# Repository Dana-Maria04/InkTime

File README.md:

# InkTime

## Block Diagram

Managed by the nRF52840 SoC, the device employs an RT6160 regulator to provide a steady 3.3V supply to all peripherals. The architecture combines an e-paper display and IMU with haptic feedback and dedicated user buttons.

## Bill of Materials (BOM)
| Qty | Value             | Parts                                                                     | Device                              | Package                      | Product Link                                                                        | Datasheet Link                                                                                                                                   |
| --: | ----------------- | ------------------------------------------------------------------------- | ----------------------------------- | ---------------------------- | ----------------------------------------------------------------------------------- | ------------------------------------------------------------------------------------------------------------------------------------------------ |
|   1 | nRF52840-QIAA     | U1                                                                        | NORDIC_NRF_4_NRF52840_QF            | AQFN-73-EP(7x7)              | [JLCPCB](https://jlcpcb.com/partdetail/NordicSemicon-NRF52840_QIAAR/C190794)        | [Datasheet](https://infocenter.nordicsemi.com/pdf/nRF52840_PS_v1.9.pdf)                                                                          |
|   1 | BQ25180YBGR       | IC1                                                                       | BQ25180YBGR                         | DSBGA-8(1.1x1.6)             | [JLCPCB](https://jlcpcb.com/partdetail/TexasInstruments-BQ25180YBGR/C3682423)       | [Datasheet](https://www.ti.com/lit/ds/symlink/bq25180.pdf)                                                                                       |
|   1 | MAX17048G+T10     | U3                                                                        | ESP32_C6_LIBRARY_MAX17048G+T10      | DFN-8-EP(2x2)                | [JLCPCB](https://jlcpcb.com/partdetail/MaximIntegrated-MAX17048GT10/C2682616)       | [Datasheet](https://www.analog.com/media/en/technical-documentation/data-sheets/MAX17048-MAX17049.pdf)                                           |
|   1 | DRV2605YZFR       | IC2                                                                       | DRV2605YZFR                         | DSBGA-9                      | [JLCPCB](https://jlcpcb.com/partdetail/TexasInstruments-DRV2605YZFR/C81079)         | [Datasheet](https://www.ti.com/lit/ds/symlink/drv2605.pdf)                                                                                       |
|   1 | DMG2305UX-7       | P-channel MOSFET                                                          | DMG2305UX-7                         | SOT-23                       | [JLCPCB](https://jlcpcb.com/partdetail/HXYMOSFET-DMG2305UX7/C5261054)               | [Datasheet](https://www.diodes.com/assets/Datasheets/DMG2305UX.pdf)                                                                              |
|   1 | SI1308EDL-T1-GE3  | Q3                                                                        | ESP32_C6_LIBRARY_6_SI1308EDL-T1-GE3 | SOT-323                      | [JLCPCB](https://jlcpcb.com/partdetail/TECHPUBLIC-SI1308EDL/C7603347)               | [Datasheet](https://www.vishay.com/docs/63399/si1308edl.pdf)                                                                                     |
|   3 | MBR0530           | D2, D4, D5                                                                | MBR0530                             | SOD-123                      | [JLCPCB](https://jlcpcb.com/partdetail/4324765-MBR0530_F20000HF/C3757235)           | [Datasheet](https://wmsc.lcsc.com/wmsc/upload/file/pdf/v2/lcsc/2205311800_Yangzhou-Yangjie-Electronic-Technology-MBR0530-F2-0000HF_C3757235.pdf) |
|   1 | USBLC6-2SC6Y      | D3                                                                        | USBLC6-2SC6Y                        | SOT-23-6                     | [JLCPCB](https://jlcpcb.com/partdetail/TECHPUBLIC-USBLC62SC6Y/C5310974)             | [Datasheet](https://wmsc.lcsc.com/wmsc/upload/file/pdf/v2/lcsc/2401261525_TECH-PUBLIC-USBLC6-2SC6Y_C5310974.pdf)                                 |
|   1 | 2450AT18B100E     | ANT1                                                                      | 2450AT18B100E_2450AT18B100E         | ANTC3216X140N / 1206 class   | [JLCPCB](https://jlcpcb.com/partdetail/JohansonTechnology-2450AT18B100/C2836414)    | [Datasheet](https://www.johansontechnology.com/datasheets/antennas/2450AT18B100.pdf)                                                             |
|   1 | KH-TYPE-C-16P     | J4                                                                        | KH-TYPE-C-16P_KH-TYPE-C-16P         | SMD                          | [JLCPCB](https://jlcpcb.com/partdetail/KH-TYPE-C-16P/C709357)                       | [Datasheet](https://wmsc.lcsc.com/wmsc/upload/file/pdf/v2/lcsc/2204251630_SHENZHEN-KINGHELM-Elec-KH-TYPE-C-16P_C709357.pdf)                      |
|   3 | EVP-AKE31A        | SW_DN, SW_ENT, SW_UP                                                      | EVP-AKE31A                          | SW_EVP-AKE31A_PAN            | [JLCPCB](https://jlcpcb.com/partdetail/PANASONIC-EVPAKE31A/C569760)                 | [Datasheet](https://www.lcsc.com/datasheet/C569760.pdf)                                                                                          |
|   1 | FTC252012SR47MBCA | L7                                                                        | MLP2016SR47MT0S1_FTC252012SR47MBCA  | INDC2016X100N                | [JLCPCB](https://jlcpcb.com/partdetail/6763488-FTC252012SR47MBCA/C5832368)          | [Datasheet](https://wmsc.lcsc.com/wmsc/upload/file/pdf/v2/lcsc/2311271530_TDK-FTC252012SR47MBCA_C5832368.pdf)                                    |
|   1 | 32.768 kHz        | X2                                                                        | NORDIC_NRF_1_XTAL_32KHZ             | SMD3215-2P                   | [JLCPCB](https://jlcpcb.com/partdetail/NDK-NX3215SA_32_768K_STD_MUA9/C519280)       | [Datasheet](https://www.ndk.com/images/products/crystal/resonator/NX3215SA_e.pdf)                                                                |
|   6 | 10K               | R2_EP_DR, R5, R7, R8, R9, R_PWR_EPD                                       | RC0201FR-1310KL                     | 0201                         | [JLCPCB](https://jlcpcb.com/partdetail/YAGEO-RC0201FR1310KL/C6373588)               | [Datasheet](https://www.lcsc.com/datasheet/C6373588.pdf)                                                                                         |
|   2 | 5K1               | R1_USB, R2_USB                                                            | RC0201FR-075K1L                     | 0201                         | [JLCPCB](https://jlcpcb.com/partdetail/YAGEO-RC0201FR075K1L/C274341)                | [Datasheet](https://www.lcsc.com/datasheet/C274341.pdf)                                                                                          |
|   2 | 3K3               | R17, R18                                                                  | RNCF0201DTC3K30                     | 0201                         | [JLCPCB](https://jlcpcb.com/partdetail/SEI_Stackpole_Elec-RNCF0201DTC3K30/C2487997) | [Datasheet](https://www.lcsc.com/datasheet/C2487997.pdf)                                                                                         |
|   3 | 0R                | R2, R3, R4                                                                | 0201WMJ0000TCE                      | 0201                         | [JLCPCB](https://jlcpcb.com/partdetail/25793-0201WMJ0000TCE/C25050)                 | [Datasheet](https://www.lcsc.com/datasheet/C25050.pdf)                                                                                           |
|   1 | 2.2Î©              | R_TYPE_SEL                                                                | 0201WMF220KTCE                      | 0201                         | [JLCPCB](https://jlcpcb.com/partdetail/244650-0201WMF220KTCE/C247442)               | [Datasheet](https://www.lcsc.com/datasheet/C247442.pdf)                                                                                          |
|   9 | 100nF             | C5, C7, C8, C12, C19, C23, C27, C34, C42                                  | AC0201KRX6S6BB104                   | 0201                         | [JLCPCB](https://jlcpcb.com/partdetail/YAGEO-AC0201KRX6S6BB104/C3855913)            | [Datasheet](https://www.lcsc.com/datasheet/C3855913.pdf)                                                                                         |
|   4 | 12pF              | C1, C2, C17, C18                                                          | 0201N120J250CT                      | 0201                         | [JLCPCB](https://jlcpcb.com/partdetail/Walsin_TechCorp-0201N120J250CT/C424835)      | [Datasheet](https://www.lcsc.com/datasheet/C424835.pdf)                                                                                          |
|   2 | 1pF               | C3, C4                                                                    | GRM0335C1E1R0CA01J                  | 0201                         | [JLCPCB](https://jlcpcb.com/partdetail/2274979-GRM0335C1E1R0CA01J/C2182912)         | [Datasheet](https://www.lcsc.com/datasheet/C2182912.pdf)                                                                                         |
|   1 | 100pF             | C11                                                                       | 0201N101F160CT                      | 0201                         | [JLCPCB](https://jlcpcb.com/partdetail/Walsin_TechCorp-0201N101F160CT/C3847857)     | [Datasheet](https://www.lcsc.com/datasheet/C3847857.pdf)                                                                                         |
|   1 | 47nF              | C16                                                                       | C0201X5R473K160NTA                  | 0201                         | [JLCPCB](https://jlcpcb.com/partdetail/126083-C0201X5R473K160NTA/C124806)           | [Datasheet](https://www.lcsc.com/datasheet/C124806.pdf)                                                                                          |
|   1 | 1uF               | C15                                                                       | CL05A105KP5NNNC                     | 0402                         | [JLCPCB](https://jlcpcb.com/partdetail/C14445)                                      | [Datasheet](https://www.lcsc.com/datasheet/C14445.pdf)                                                                                           |
|   5 | 4.7uF             | C6, C14, C20, C21, C43                                                    | GRM155R61A475KEAAD                  | 0402                         | [JLCPCB](https://jlcpcb.com/partdetail/MurataElectronics-GRM155R61A475KEAAD/C77004) | [Datasheet](https://www.lcsc.com/datasheet/C77004.pdf)                                                                                           |
|   1 | 4.7uF / 25V       | C2-EP-DR                                                                  | C0402X5R475M250NT                   | 0402                         | [JLCPCB](https://jlcpcb.com/partdetail/SANYEAR-C0402X5R475M250NT/C2911388)          | [Datasheet](https://www.lcsc.com/datasheet/C2911388.pdf)                                                                                         |
|   9 | 1uF / 50V         | EPD_C1, EPD_C2, EPD_C6, EPD_C7, EPD_C8, EPD_C9, EPD_C10, EPD_C11, EPD_C12 | GRM155R61H105KE05D                  | 0402                         | [JLCPCB](https://jlcpcb.com/partdetail/1609005-GRM155R61H105KE05D/C1518208)         | [Datasheet](https://www.lcsc.com/datasheet/C1518208.pdf)                                                                                         |
|   2 | 10uF              | C24, C39                                                                  | 0402X106M100CT                      | 0402                         | [JLCPCB](https://jlcpcb.com/partdetail/Walsin_TechCorp-0402X106M100CT/C2992625)     | [Datasheet](https://www.lcsc.com/datasheet/C2992625.pdf)                                                                                         |
|   2 | 22uF              | C25, C33                                                                  | CL05A226MQ6ZUN8                     | 0402                         | [JLCPCB](https://jlcpcb.com/partdetail/2889851-CL05A226MQ6ZUN8/C2762589)            | [Datasheet](https://www.lcsc.com/datasheet/C2762589.pdf)                                                                                         |
|   1 | 820pF             | C9                                                                        | MA0201XF821K250                     | 0201                         | [JLCPCB](https://jlcpcb.com/partdetail/Meritek-MA0201XF821K250/C3842403)            | [Datasheet](https://www.lcsc.com/datasheet/C3842403.pdf)                                                                                         |
|   1 | 32MHz             | X1                                                                        | NX2016SA-32MHZ-STD-CZS-5            | SMD2016-4P                   | [JLCPCB](https://jlcpcb.com/partdetail/NDK-NX2016SA_32MHZ_STD_CZS5/C843260)         | [Datasheet](https://www.lcsc.com/datasheet/C843260.pdf)                                                                                          |
|   1 | 3.9nH             | L1                                                                        | VHF060303H3N9ST                     | 0201                         | [JLCPCB](https://jlcpcb.com/partdetail/153834-VHF060303H3N9ST/C142503)              | [Datasheet](https://www.lcsc.com/datasheet/C142503.pdf)                                                                                          |
|   1 | 15nH              | L3                                                                        | MLK0603L15NJT000                    | 0201                         | [JLCPCB](https://jlcpcb.com/partdetail/TDK-MLK0603L15NJT000/C6990407)               | [Datasheet](https://www.lcsc.com/datasheet/C6990407.pdf)                                                                                         |
|   1 | BMA421            | IC3                                                                       | BMA421                              | LGA-12(2x2)                  | [JLCPCB](https://jlcpcb.com/partdetail/BoschSensortec-BMA421/C5242966)              | [Datasheet](https://files.pine64.org/doc/datasheet/pinetime/BST-BMA421-FL000.pdf)                                                                |
|   1 | RT6160AWSC        | IC9                                                                       | RT6160AWSC                          | WLCSP-15B(2.3x1.4)           | [JLCPCB](https://jlcpcb.com/partdetail/RichtekTech-RT6160AWSC/C7065276)             | [Datasheet](https://www.mouser.com/datasheet/2/1458/DS6160A_03-3104604.pdf)                                                                      |
|   1 | 503480-2400       | J1                                                                        | 5034802400                          | 24-pin 0.5mm right-angle FPC | [JLCPCB](https://jlcpcb.com/partdetail/MOLEX-5034802400/C122434)                    | [Datasheet](https://www.mouser.com/datasheet/2/276/2/5034802400_FFC_FPC_CONNECTORS-1112921.pdf)                                                  |

## System Design and Hardware Implementation

The hardware architecture of the **InkTime Smartwatch** centers on the **nRF52840 microcontroller**, integrating five specialized sub-systems to create a high-efficiency wearable device.

### 1. Central SoC & Communication
The **nRF52840** handles all high-level logic, from sensor fusion to Bluetooth LE communication. It utilizes a **32 MHz crystal** for active processing and a **32.768 kHz crystal** for low-power timekeeping. For debugging and firmware updates, a **TC2030 SWD header** is included, exposing the `SWDIO` and `SWDCLK` lines.

### 2. Power Subsystem & Efficiency
Energy is managed through a multi-stage architecture:
* **USB-C Input:** Protected by **USBLC6-2SC6Y** ESD diodes to ensure safety during charging.
* **Management:** The **BQ25180 charger** regulates power flow between the USB source and the **Li-Po battery**.
* **Efficiency:** An **RT6160 Buck-Boost converter** ensures all peripherals receive exactly **3.3V**, regardless of battery discharge levels.
* **Monitoring:** The **MAX17048 fuel gauge** uses I2C to alert the MCU of low-battery conditions in real-time.

### 3. Specialized Sub-systems
* **Display:** The **1.54-inch E-Ink panel** uses an SPI interface. Its bi-stable nature allows it to hold an image without consuming power, drastically reducing the overall energy profile.
* **Motion & Interaction:** An **IMU (BMA421/423)** monitors activity, while three GPIO-mapped buttons manage user navigation and input.
* **Haptics:** Physical feedback for notifications is provided by a vibration motor controlled by the **DRV2605 driver**, which supports pre-programmed haptic patterns over I2C.

### 4. Energy Estimation
The system is optimized for an extremely low duty cycle:
* **Deep Sleep:** $< 10\text{µ}$.
* **Active Refresh:** $8\text{-}10\text{ mA}$ for approximately $1\text{-}2$ seconds per minute.

Based on the **250 mAh** battery capacity, the smartwatch achieves an autonomy of **over 9 days**, even with active sensor monitoring and daily haptic notifications. This performance highlights the synergy between the E-Ink technology and the nRF52's advanced power-saving features.

### Detailed Pinnout Map of nRF52840

| nRF52840 Pin | Connected Block | Signal Name | Purpose / Function |
| :--- | :--- | :--- | :--- |
| **P1.13** | E-paper Display | `MOSI` | SPI data output to display |
| **P1.15** | E-paper Display | `SCK` | SPI serial clock line |
| **P0.05** | E-paper Display | `EPD_CS` | SPI chip select (active low) |
| **P0.16** | E-paper Display | `EPD_DC` | Data/Command selection toggle |
| **P0.17** | E-paper Display | `EPD_RST` | Hardware reset for display |
| **P0.15** | E-paper Display | `EPD_BUSY` | Status feedback (busy/ready) |
| **P0.06** | I2C Bus (Shared) | `SDA` | Data line for IMU, Fuel Gauge, and Haptic |
| **P0.07** | I2C Bus (Shared) | `SCL` | Clock line for IMU, Fuel Gauge, and Haptic |
| **P0.08** | IMU (BMA42x) | `IMU_INT1` | Primary motion interrupt |
| **P1.08** | IMU (BMA42x) | `IMU_INT2` | Secondary motion interrupt |
| **P0.11** | PMIC (BQ25180) | `PMIC_INT` | Power-management status interrupt |
| **P0.24** | Fuel Gauge | `ALERT` | Battery fuel gauge status alert |
| **P0.12** | Haptic Driver | `HAPTIC_EN` | Enable and control for DRV2605 |
| **P0.13** | USB-C Interface | `D+` | USB differential data positive |
| **P0.14** | USB-C Interface | `D-` | USB differential data negative |
| **VBUS pin** | Charger / USB-C | `VBUS` | USB voltage presence detection |
| **SWDIO** | SWD Header | `SWDIO` | Bidirectional debug/programming data |
| **SWDCLK** | SWD Header | `SWDCLK` | Debug/programming clock reference |
| **P1.09** | SWD Header | `SWO` | Single Wire Output (trace debug) |
| **P0.18 / RESET** | SWD Header | `RESET` | Global hardware reset line |
| **ANT pin** | RF Network | `RF` | 2.4 GHz connection to chip antenna |

## Design Decisions & DRC/ERC Notes

### 1. Hardware Design Log
* **Space Optimization:** To fit the enclosure, a **1.0 mm PCB** was used with all components mounted on the **TOP layer**. The use of **0201 footprints** was critical for the high-density layout.
* **Signal Integrity:** **100 nF decoupling capacitors** are placed as close as possible ($< 0.5$ mm) to power pins. Power traces are widened to **0.3 mm** to ensure stable voltage delivery.
* **RF Layout:** The antenna is positioned on the board edge with a clear **Keep-out zone** (no copper on any layer) to maximize Bluetooth connectivity.

### 2. Validation & Manual Approvals
The following CAD warnings were reviewed and approved based on project constraints:

* **Mechanical Alignment (DRC):** Dimension errors for the **USB-C connector and tactile buttons** were ignored because their placement must match the pre-defined enclosure openings.
* **High-Density Routing (DRC):** Overlaps caused by **via-in-pad** and escape routing for the nRF52840 were accepted. This was the only way to route the MCU pins in the available space.
* **Net Connectivity (ERC):** "Only INPUT pins" warnings were verified; the schematic is functionally complete, and these are typical false positives in this project context.
* **Power Pins (ERC):** Power rail warnings were manually checked to ensure that the **RT6160** and **BQ25180** correctly supply the 3.3V and VBAT nets.

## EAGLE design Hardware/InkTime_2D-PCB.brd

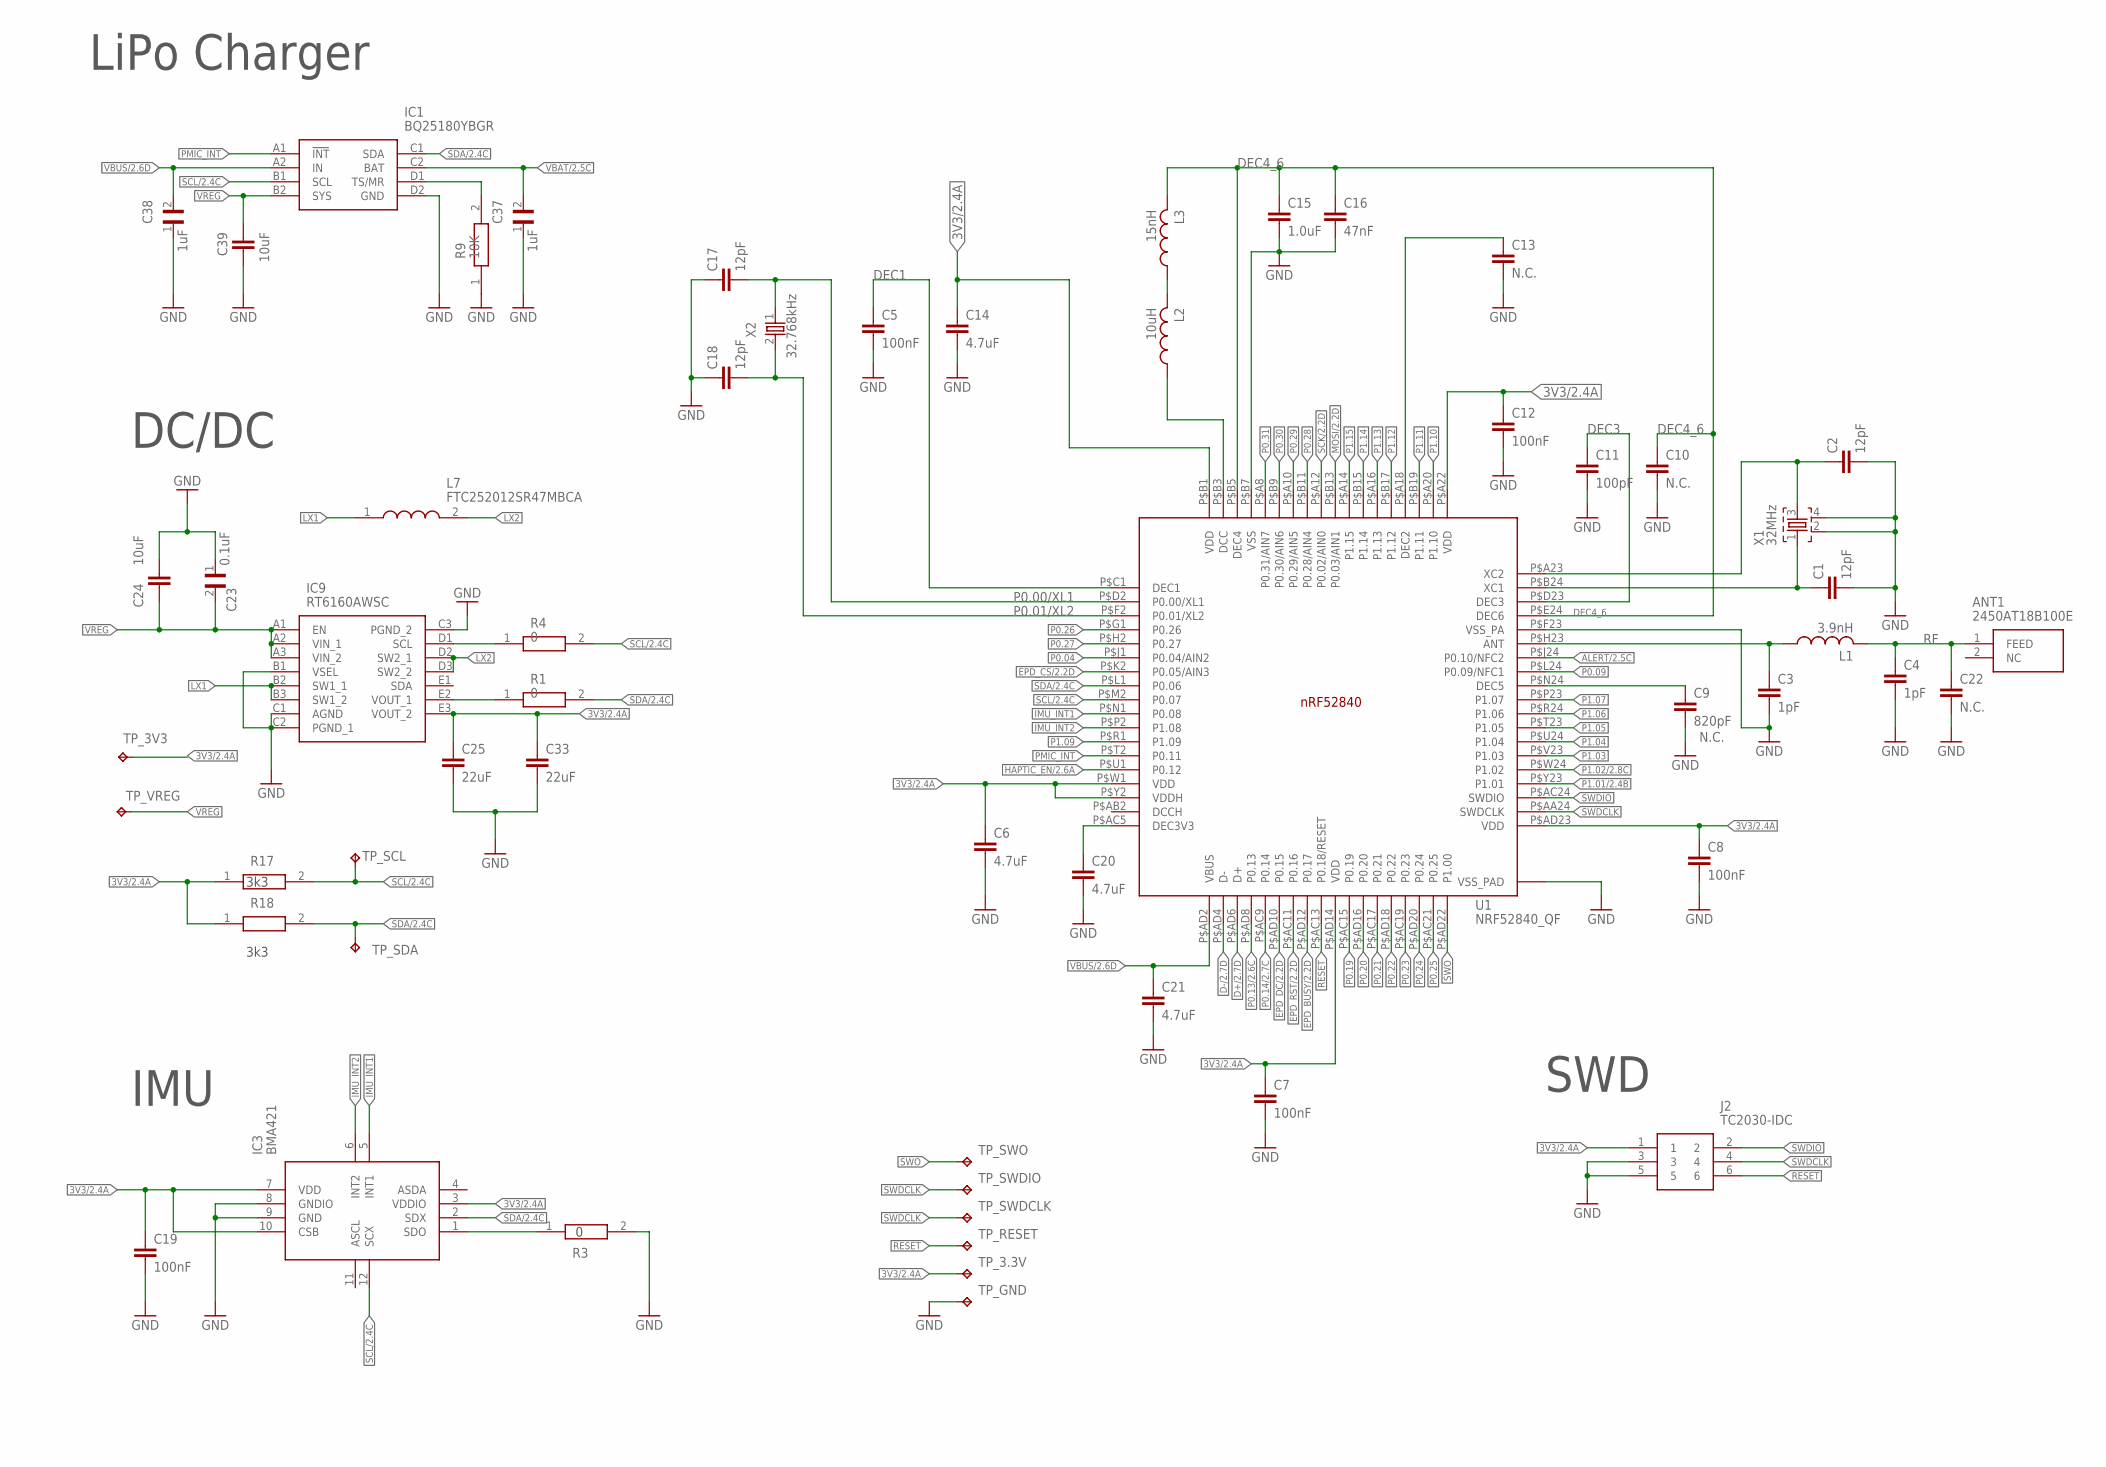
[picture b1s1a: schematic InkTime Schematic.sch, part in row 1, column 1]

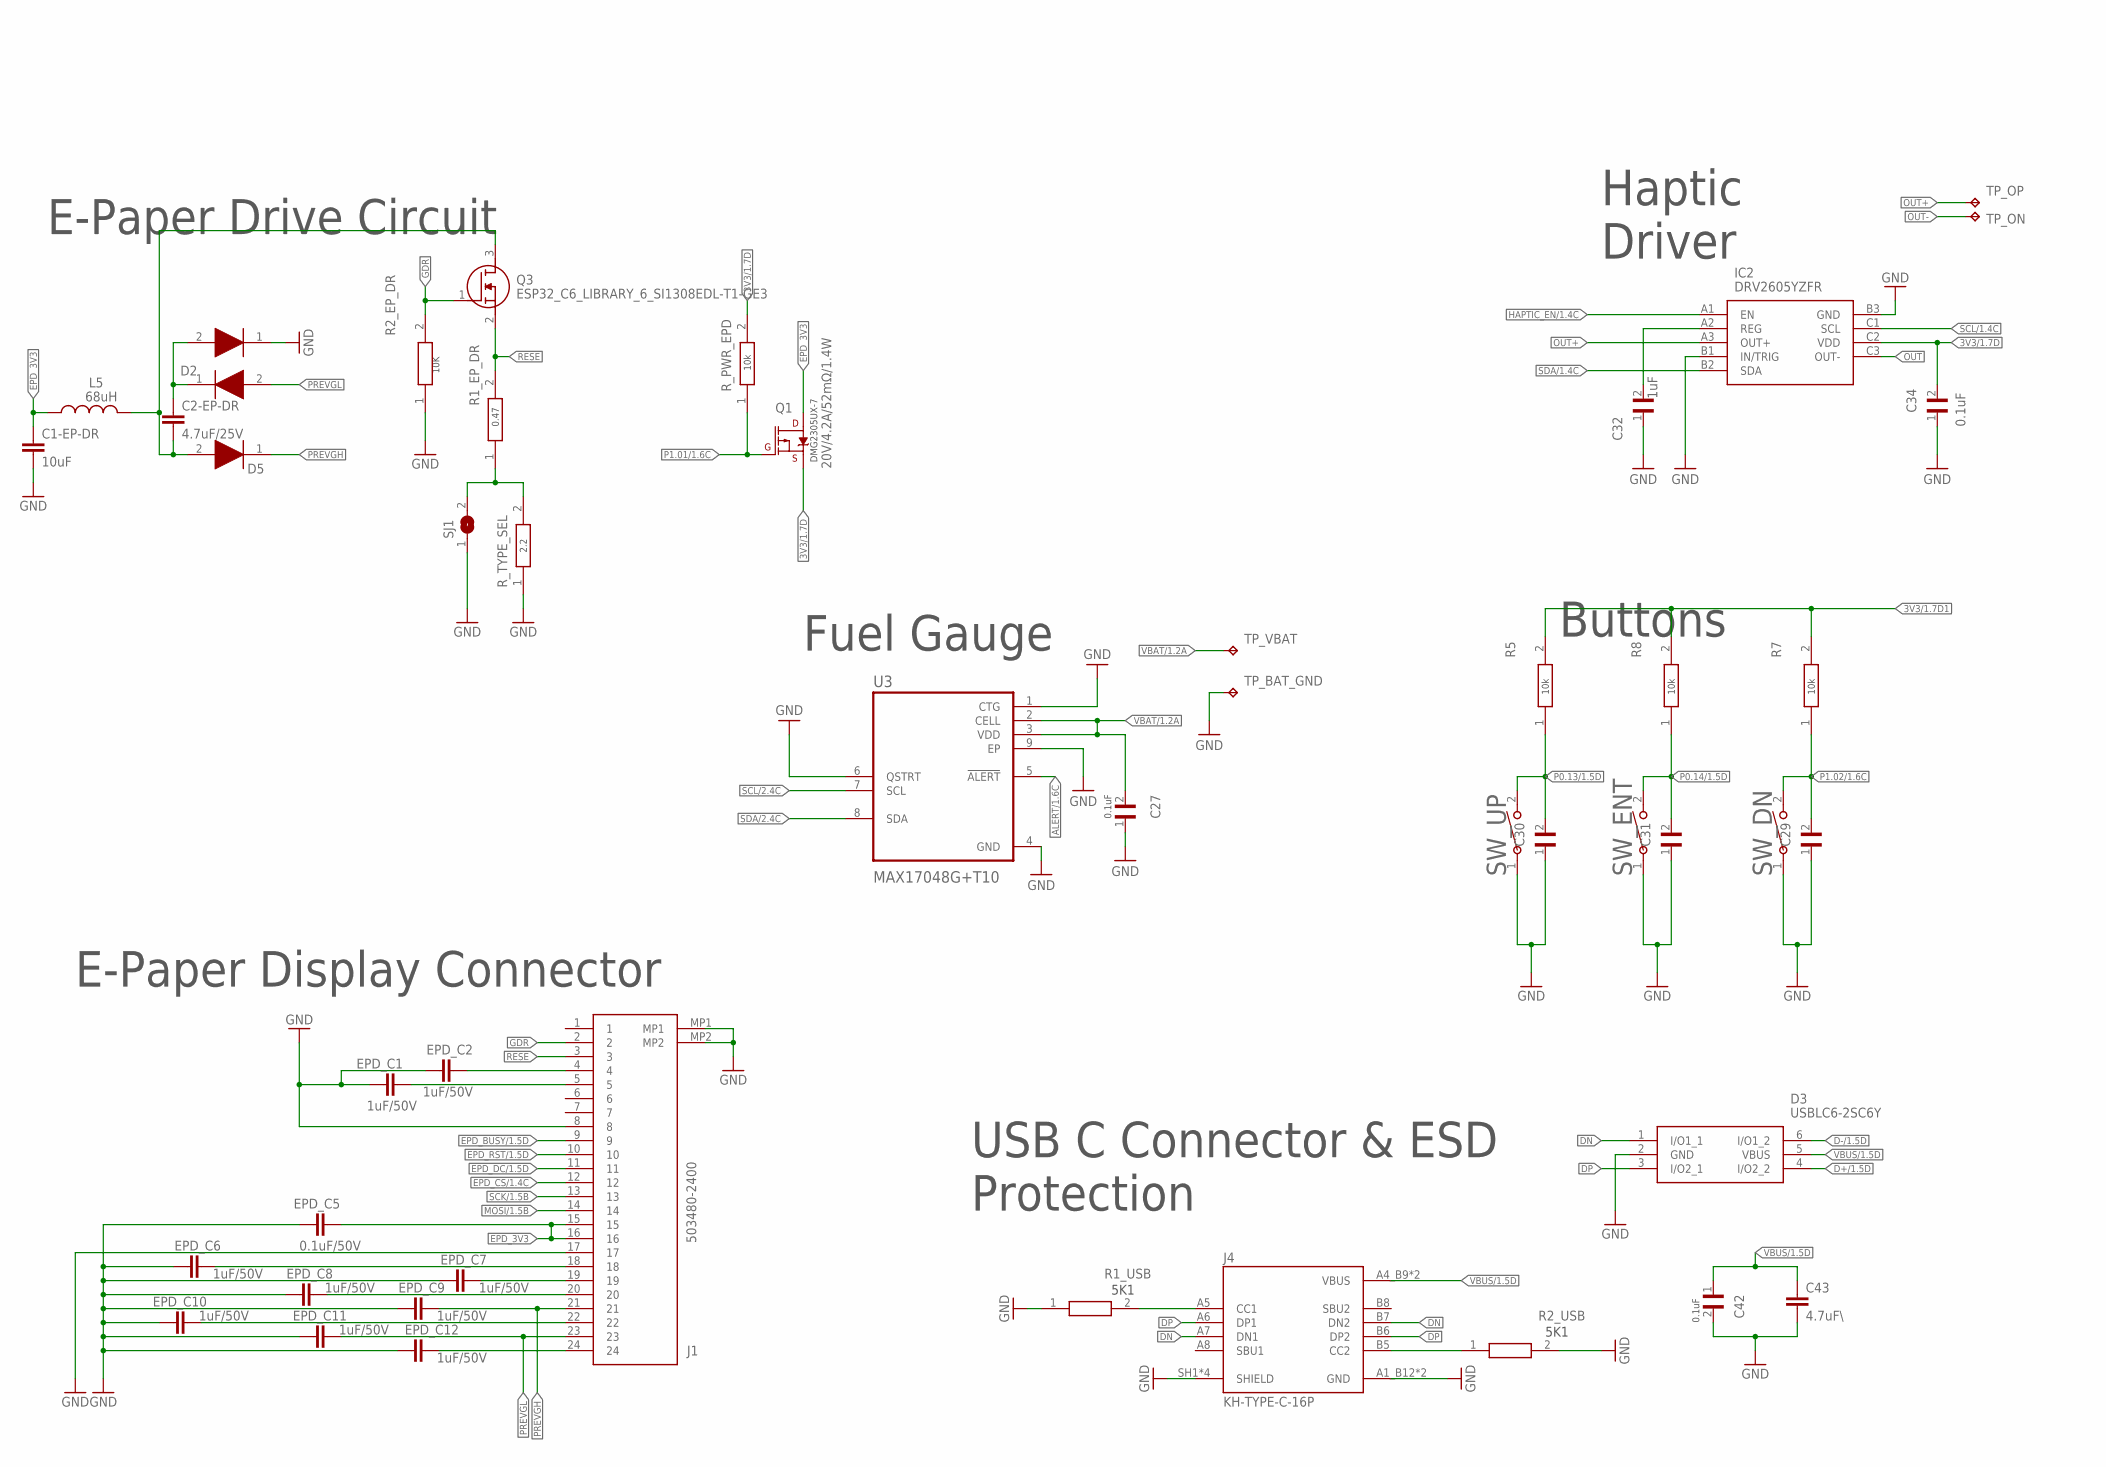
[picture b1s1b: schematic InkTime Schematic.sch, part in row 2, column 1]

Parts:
ANT1: 2450AT18B100E; 2450AT18B100E_ANTC3216X140N
C1, C2, C17, C18: 12pF; NORDIC_NRF_3_RESC0201_L
C1-EP-DR, C24, C39: 10uF; NORDIC_NRF_3_RESC0402_L
C2-EP-DR: 4.7uF/25V; NORDIC_NRF_3_RESC0402_L
C3, C4: 1pF; NORDIC_NRF_3_RESC0201_L
C5, C7, C8, C12, C19: 100nF; NORDIC_NRF_3_RESC0201_L
C6, C14: 4.7uF; NORDIC_NRF_3_RESC0402_L
C9: 820pF; NORDIC_NRF_3_RESC0201_L
C10, C13, C22: N.C.; NORDIC_NRF_3_RESC0201_L
C11: 100pF; NORDIC_NRF_3_RESC0201_L
C15: 1.0uF; NORDIC_NRF_3_RESC0402_L
C16: 47nF; NORDIC_NRF_3_RESC0201_L
C20, C21: 4.7uF; PERFECT_0402_0402
C23, C27, C34: 0.1uF; GRM011R60J152KE01L_1_0201
C25, C33: 22uF; NORDIC_NRF_3_RESC0402_L
C29, C30, C31: 1uF; GRM011R60J152KE01L_2_CAPC0201X13N
C32, C37, C38: 1uF; GRM011R60J152KE01L_1_0201
C42: 0.1uF; GRM011R60J152KE01L_2_CAPC0201X13N
C43: 4.7uF\; NORDIC_NRF_3_RESC0402_L
D1: MBR0530; ESP32_C6_LIBRARY_5_SOD3716X135N
D2, D5: ESP32_C6_LIBRARY_5_MBR0530; ESP32_C6_LIBRARY_5_SOD3716X135N
D3: USBLC6-2SC6Y; ESP32_C6_LIBRARY_3_SOT95P280X145-6N
EPD_C1, EPD_C2, EPD_C6, EPD_C7, EPD_C8, EPD_C9, EPD_C10, EPD_C11, EPD_C12: 1uF/50V; NORDIC_NRF_3_RESC0402_L
EPD_C5: 0.1uF/50V; NORDIC_NRF_3_RESC0201_L
IC1: BQ25180YBGR; BQ25180YBGR_BGA8C40P2X4_100X155X50
IC2: DRV2605YZFR; DRV2605YZFR_BGA9C50P3X3_144X144X62
IC3: BMA421; BMA423_BMA423
IC9: RT6160AWSC; RT6160AWSC_BGA15C40P3X5_140X230X60
J1: 503480-2400; 503480-2400_5034802400
J2: TC2030-IDC; TC2030-IDC_TC2030IDC
J4: KH-TYPE-C-16P; KH-TYPE-C-16P_KINGHELM_KH-TYPE-C-16P
L1: 3.9nH; NORDIC_NRF_2_RESC0201_L
L2: 10uH; NORDIC_NRF_2_RESC0201_L
L3: 15nH; NORDIC_NRF_2_RESC0201_L
L5: 68uH; NORDIC_NRF_2_RESC0402_L
L7: FTC252012SR47MBCA; MLP2016SR47MT0S1_INDC2016X100N
Q1: 20V/4.2A/52mΩ/1.4W; ESP32_C6_LIBRARY_4_ESP32_C6_LIBRARY_4_ESP32_C6_LIBRARY_4_ES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
Q3: ESP32_C6_LIBRARY_6_SI1308EDL-T1-GE3; ESP32_C6_LIBRARY_6_SOT65P210X110-3N
R1, R3, R4: 0; ERA-1AEB3401C_0201
R1_EP_DR: 0.47; CPF0201D7K68C1_0201
R1_USB, R2_USB: 5K1; CPF0201D7K68C1_0201
R2_EP_DR, R5, R7, R8: 10k; CPF0201D7K68C1_0201
R9: 10K; ERA-1AEB3401C_0201
R17: 3k3; ERA-1AEB3401C_0201
R18: 3K3; ERA-1AEB3401C_0201
R_PWR_EPD: 10K; CPF0201D7K68C1_0201
R_TYPE_SEL: 2.2; CPF0201D7K68C1_0201
SJ1: ESP32_C6_LIBRARY_7_JUMPER_SJ
SW_DN: 2025-10-22_07-23-44_LIBRARY_EVP-AKE31ASW_EVP-AKE3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; 2025-10-22_07-23-44_LIBRARY_SW_EVP-AKE31A_PAN
SW_ENT: 2025-10-22_07-23-44_LIBRARY_EVP-AKE31ASW_EVP-AKE3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; 2025-10-22_07-23-44_LIBRARY_SW_EVP-AKE31A_PAN
SW_UP: 2025-10-22_07-23-44_LIBRARY_EVP-AKE31ASW_EVP-AKE3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; 2025-10-22_07-23-44_LIBRARY_SW_EVP-AKE31A_PAN
TP_3.3V, TP_3V3: HECTOR_WATCH_1_TPTP20R; HECTOR_WATCH_1_TP20R
TP_BAT_GND: HECTOR_WATCH_1_TPTP20R; HECTOR_WATCH_1_TP20R
TP_GND: HECTOR_WATCH_1_TPTP20R; HECTOR_WATCH_1_TP20R
TP_ON: HECTOR_WATCH_1_TPTP20R; HECTOR_WATCH_1_TP20R
TP_OP: HECTOR_WATCH_1_TPTP20R; HECTOR_WATCH_1_TP20R
TP_RESET: HECTOR_WATCH_1_TPTP20R; HECTOR_WATCH_1_TP20R
TP_SCL: HECTOR_WATCH_1_TPTP20R; HECTOR_WATCH_1_TP20R
TP_SDA: HECTOR_WATCH_1_TPTP20R; HECTOR_WATCH_1_TP20R
TP_SWDCLK: HECTOR_WATCH_1_TPTP20R; HECTOR_WATCH_1_TP20R
TP_SWDIO: HECTOR_WATCH_1_TPTP20R; HECTOR_WATCH_1_TP20R
TP_SWO: HECTOR_WATCH_1_TPTP20R; HECTOR_WATCH_1_TP20R
TP_VBAT: HECTOR_WATCH_1_TPTP20R; HECTOR_WATCH_1_TP20R
TP_VREG: HECTOR_WATCH_1_TPTP20R; HECTOR_WATCH_1_TP20R
U1: NRF52840_QF; NORDIC_NRF_4_AQFN50P700X700X85_HS-74N
U3: MAX17048G+T10; ESP32_C6_LIBRARY_SON50P200X200X80-9N
X1: 32MHz; NORDIC_NRF_BT-XTAL_2016_N
X2: 32.768kHz; NORDIC_NRF_1_XTAL_3215_N

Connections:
3V3/1.7D: C34.2, IC2.C2 (VDD), Q1.2 (S), R_PWR_EPD.2
3V3/1.7D1: R5.2, R7.2, R8.2
3V3/2.4A: C6.1, C7.1, C8.1, C12.1, C14.1, C19.1, C25.1, C33.1, IC3.3 (VDDIO), IC3.7 (VDD), IC3.10 (CSB), IC9.E3 (VOUT_2), J2.1, R17.1, R18.1, TP_3.3V.TP, TP_3V3.TP, U1.P$A22 (VDD), U1.P$AD14 (VDD), U1.P$AD23 (VDD), U1.P$B1 (VDD), U1.P$W1 (VDD), U1.P$Y2 (VDDH)
ALERT/1.6C: U3.5 (!ALERT)
ALERT/2.5C: U1.P$J24 (P0.10/NFC2)
D+/1.5D: D3.4 (I/O2_2)
D+/2.7D: U1.P$AD6 (D+)
D-/1.5D: D3.6 (I/O1_2)
D-/2.7D: U1.P$AD4 (D-)
DEC1: C5.1, U1.P$C1 (DEC1)
DEC3: C11.1, U1.P$D23 (DEC3)
DEC4_6: C10.1, C15.1, C16.1, L3.2, U1.P$B5 (DEC4), U1.P$E24 (DEC6)
DN: D3.1 (I/O1_1), J4.A7 (DN1), J4.B7 (DN2)
DP: D3.3 (I/O2_1), J4.A6 (DP1), J4.B6 (DP2)
EPD_3V3: C1-EP-DR.1, EPD_C5.2, J1.15, J1.16, L5.1, Q1.3 (D)
EPD_BUSY/1.5D: J1.9
EPD_BUSY/2.2D: U1.P$AD12 (P0.17)
EPD_CS/1.4C: J1.12
EPD_CS/2.2D: U1.P$K2 (P0.05/AIN3)
EPD_DC/1.5D: J1.11
EPD_DC/2.2D: U1.P$AD10 (P0.15)
EPD_RST/1.5D: J1.10
EPD_RST/2.2D: U1.P$AC11 (P0.16)
GDR: J1.2, Q3.1 (G), R2_EP_DR.2
GND: C1.2, C1-EP-DR.2, C2.2, C3.2, C4.2, C5.2, C6.2, C7.2, C8.2, C11.2, C12.2, C13.2, C14.2, C17.1, C18.1, C19.2, C20.2, C21.2, C22.2, C23.1, C24.1, C25.2, C27.1, C29.1, C30.1, C31.1, C32.1, C33.2, C34.1, C37.1, C38.1, C39.1, C42.2, C43.2, D1.1 (K), D3.2 (GND), EPD_C1.1, EPD_C2.1, EPD_C5.1, EPD_C6.1, EPD_C7.1, EPD_C8.1, EPD_C9.1, EPD_C10.1, EPD_C11.1, EPD_C12.1, IC1.D2 (GND), IC2.B1 (IN/TRIG), IC2.B3 (GND), IC3.8 (GNDIO), IC3.9 (GND), IC9.B1 (VSEL), IC9.C1 (AGND), IC9.C2 (PGND_1), IC9.C3 (PGND_2), J1.8, J1.17, J1.MP1, J1.MP2, J2.3, J2.5, J4.A1_B12 (GND), J4.A12_B1 (GND), J4.SH1 (SHIELD), J4.SH2 (SHIELD), J4.SH3 (SHIELD), J4.SH4 (SHIELD), R1_USB.1, R2_EP_DR.1, R2_USB.2, R3.2, R9.1, R_TYPE_SEL.1, SJ1.1, SW_DN.1, SW_ENT.1, SW_UP.1, TP_BAT_GND.TP, TP_GND.TP, U1.P$74 (VSS_PAD), U1.P$75 (VSS_PAD), U1.P$76 (VSS_PAD), U1.P$77 (VSS_PAD), U1.P$78 (VSS_PAD), U1.P$79 (VSS_PAD), U1.P$80 (VSS_PAD), U1.P$81 (VSS_PAD), U1.P$82 (VSS_PAD), U1.P$83 (VSS_PAD), U1.P$84 (VSS_PAD), U1.P$85 (VSS_PAD), U1.P$86 (VSS_PAD), U1.P$87 (VSS_PAD), U1.P$88 (VSS_PAD), U1.P$89 (VSS_PAD), U1.P$90 (VSS_PAD), U1.P$F23 (VSS_PA), U3.1 (CTG), U3.4 (GND), U3.6 (QSTRT), U3.9 (EP), X1.2, X1.4
HAPTIC_EN/1.4C: IC2.A1 (EN)
HAPTIC_EN/2.6A: U1.P$U1 (P0.12)
IMU_INT1: IC3.5 (INT1), U1.P$N1 (P0.08)
IMU_INT2: IC3.6 (INT2), U1.P$P2 (P1.08)
LX1: IC9.B2 (SW1_1), IC9.B3 (SW1_2), L7.1
LX2: IC9.D2 (SW2_1), IC9.D3 (SW2_2), L7.2
MOSI/1.5B: J1.14
MOSI/2.2D: U1.P$B13 (P0.03/AIN1)
unnamed: C20.1, U1.P$AC5 (DEC3V3)
unnamed: C9.1, U1.P$N24 (DEC5)
unnamed: C13.1, U1.P$A18 (DEC2)
unnamed: L2.2, L3.1
unnamed: C15.2, C16.2, U1.P$B7 (VSS)
unnamed: L2.1, U1.P$B3 (DCC)
unnamed: C3.1, L1.1, U1.P$H23 (ANT)
unnamed: C2.1, U1.P$A23 (XC2), X1.3
unnamed: C1.1, U1.P$B24 (XC1), X1.1
unnamed: EPD_C2.2, J1.4
unnamed: IC9.D1 (SCL), R4.1
unnamed: EPD_C10.2, J1.22
unnamed: IC9.E2 (VOUT_1), R1.1
unnamed: EPD_C1.2, J1.5
unnamed: IC1.D1 (TS/MR), R9.2
unnamed: IC3.1 (SDO), R3.1
unnamed: EPD_C6.2, J1.18
unnamed: EPD_C7.2, J1.19
unnamed: EPD_C12.2, J1.24
unnamed: EPD_C8.2, J1.20
unnamed: C32.2, IC2.A2 (REG)
unnamed: C2-EP-DR.2, D5.2 (A), L5.2, Q3.3 (D)
unnamed: C2-EP-DR.1, D1.2 (A), D2.1 (K)
unnamed: R1_EP_DR.1, R_TYPE_SEL.2, SJ1.2
unnamed: J4.A5 (CC1), R1_USB.2
unnamed: J4.B5 (CC2), R2_USB.1
N.C.: C9.2, C10.2
OUT: IC2.C3 (OUT-)
OUT+: IC2.A3 (OUT+), TP_OP.TP
OUT-: TP_ON.TP
P0.00/XL1: C17.2, U1.P$D2 (P0.00/XL1), X2.1
P0.01/XL2: C18.2, U1.P$F2 (P0.01/XL2), X2.2
P0.04: U1.P$J1 (P0.04/AIN2)
P0.09: U1.P$L24 (P0.09/NFC1)
P0.13/1.5D: C30.2, R5.1, SW_UP.2
P0.13/2.6C: U1.P$AD8 (P0.13)
P0.14/1.5D: C31.2, R8.1, SW_ENT.2
P0.14/2.7C: U1.P$AC9 (P0.14)
P0.19: U1.P$AC15 (P0.19)
P0.20: U1.P$AD16 (P0.20)
P0.21: U1.P$AC17 (P0.21)
P0.22: U1.P$AD18 (P0.22)
P0.23: U1.P$AC19 (P0.23)
P0.24: U1.P$AD20 (P0.24)
P0.25: U1.P$AC21 (P0.25)
P0.26: U1.P$G1 (P0.26)
P0.27: U1.P$H2 (P0.27)
P0.28: U1.P$B11 (P0.28/AIN4)
P0.29: U1.P$A10 (P0.29/AIN5)
P0.30: U1.P$B9 (P0.30/AIN6)
P0.31: U1.P$A8 (P0.31/AIN7)
P1.01/1.6C: Q1.1 (G), R_PWR_EPD.1
P1.01/2.4B: U1.P$Y23 (P1.01)
P1.02/1.6C: C29.2, R7.1, SW_DN.2
P1.02/2.8C: U1.P$W24 (P1.02)
P1.03: U1.P$V23 (P1.03)
P1.04: U1.P$U24 (P1.04)
P1.05: U1.P$T23 (P1.05)
P1.06: U1.P$R24 (P1.06)
P1.07: U1.P$P23 (P1.07)
P1.09: U1.P$R1 (P1.09)
P1.10: U1.P$A20 (P1.10)
P1.11: U1.P$B19 (P1.11)
P1.12: U1.P$B17 (P1.12)
P1.13: U1.P$A16 (P1.13)
P1.14: U1.P$B15 (P1.14)
P1.15: U1.P$A14 (P1.15)
PMIC_INT: IC1.A1 (!INT), U1.P$T2 (P0.11)
PREVGH: D5.1 (K), EPD_C9.2, J1.21
PREVGL: D2.2 (A), EPD_C11.2, J1.23
RESE: J1.3, Q3.2 (S), R1_EP_DR.2
RESET: J2.6, TP_RESET.TP, U1.P$AC13 (P0.18/RESET)
RF: ANT1.1 (FEED), C4.1, C22.1, L1.2
SCK/1.5B: J1.13
SCK/2.2D: U1.P$A12 (P0.02/AIN0)
SCL/1.4C: IC2.C1 (SCL)
SCL/2.4C: IC1.B1 (SCL), IC3.12 (SCX), R4.2, R17.2, TP_SCL.TP, U1.P$M2 (P0.07), U3.7 (SCL)
SDA/1.4C: IC2.B2 (SDA)
SDA/2.4C: IC1.C1 (SDA), IC3.2 (SDX), R1.2, R18.2, TP_SDA.TP, U1.P$L1 (P0.06), U3.8 (SDA)
SWDCLK: J2.4, TP_SWDCLK.TP, TP_SWDIO.TP, U1.P$AA24 (SWDCLK)
SWDIO: J2.2, U1.P$AC24 (SWDIO)
SWO: TP_SWO.TP, U1.P$AD22 (P1.00)
VBAT/1.2A: C27.2, TP_VBAT.TP, U3.2 (CELL), U3.3 (VDD)
VBAT/2.5C: C37.2, IC1.C2 (BAT)
VBUS/1.5D: C42.1, C43.1, D3.5 (VBUS), J4.A4_B9 (VBUS), J4.A9_B4 (VBUS)
VBUS/2.6D: C21.1, C38.2, IC1.A2 (IN), U1.P$AD2 (VBUS)
VREG: C23.2, C24.2, C39.2, IC1.B2 (SYS), IC9.A1 (EN), IC9.A2 (VIN_1), IC9.A3 (VIN_2), TP_VREG.TP

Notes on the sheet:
SWD
LiPo Charger
IMU
DC/DC
E-Paper Display Connector
3k3
Fuel Gauge
0.1uF
E-Paper Drive Circuit
0.47
2.2
10K
DMG2305UX-7
10k
Haptic Driver
5K1
USB C Connector & ESD Protection
Buttons

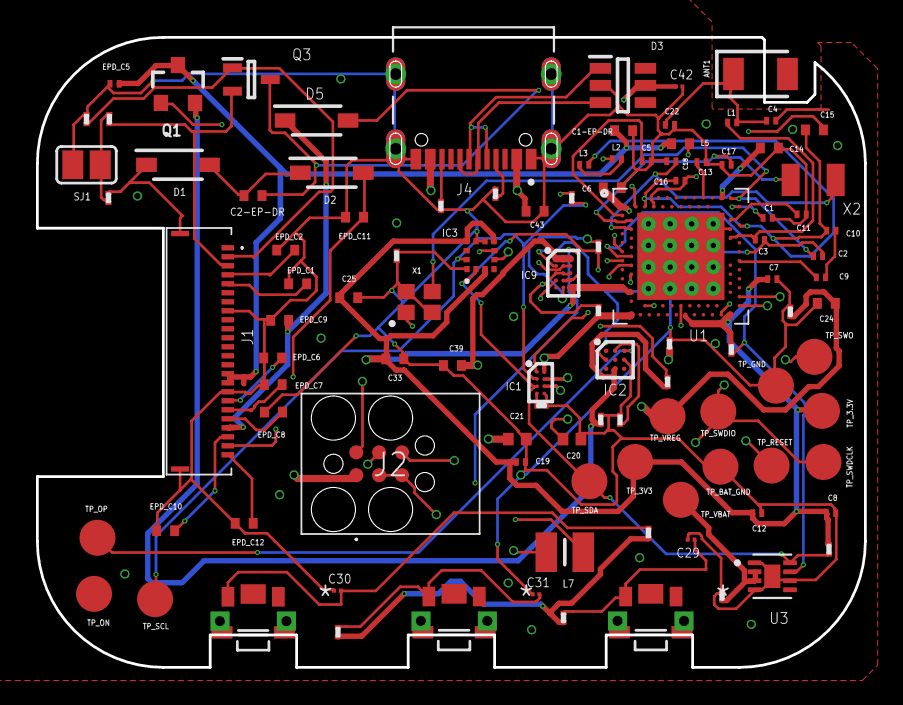
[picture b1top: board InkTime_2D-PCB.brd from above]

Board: 4 copper layers, 46.0 x 35.0 mm, 105 parts (0 on the bottom side), 65 nets.

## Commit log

2026-04-21 Updated 2D-PCB Fixes #6
2026-04-21 Added images with the renders of the device
    Fixes #3
2026-04-21 Added mechanical files
    Fixes #2
2026-04-21 Add schematic print-out
    Fixes #1
2026-04-21 Update Schematic
    Fixes #5
2026-04-21 Update Manufacturing Files
2026-04-21 Enhance README with block diagram and BOM details
    Added detailed block diagram, BOM, system design, and hardware implementation sections to the README.

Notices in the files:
parts and their libraries:
InkTime_v5: COPYRIGHT: Copyright (C) 2025 Ultra Librarian. All rights reserved.
